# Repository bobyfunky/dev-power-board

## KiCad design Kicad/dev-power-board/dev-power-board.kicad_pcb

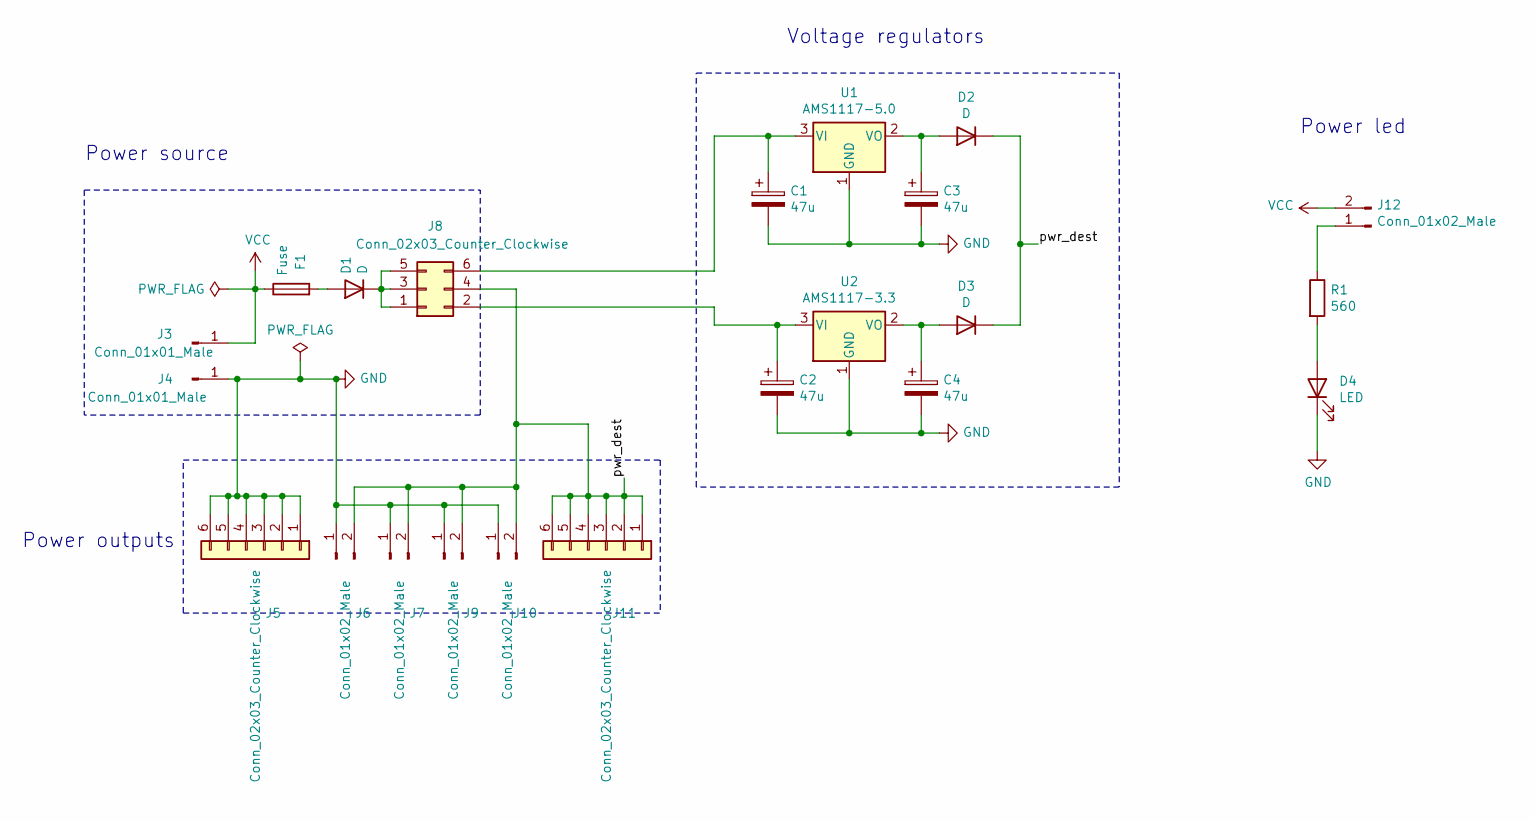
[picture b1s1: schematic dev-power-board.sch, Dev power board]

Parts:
C1, C2, C3, C4: 47u; CP_Elec_6.3x5.4
D1, D2, D3: D; D_0805_2012Metric_Pad1.15x1.40mm_HandSolder
D4: LED; LED_0805_2012Metric
F1: Fuse; Fuse_0805_2012Metric_Pad1.15x1.40mm_HandSolder
J3, J4: Conn_01x01_Male; Banana_Jack_1Pin
J5, J11: Conn_02x03_Counter_Clockwise; PinHeader_1x06_P2.54mm_Vertical
J6, J7, J9, J10, J12: Conn_01x02_Male; PinHeader_1x02_P2.54mm_Vertical
J8: Conn_02x03_Counter_Clockwise; PinHeader_2x03_P2.54mm_Vertical
R1: 560; R_0805_2012Metric_Pad1.15x1.40mm_HandSolder
U1: AMS1117-5.0; SOT-223-3_TabPin2
U2: AMS1117-3.3; SOT-223-3_TabPin2

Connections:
/pwr_dest: D2.1 (K), D3.1 (K), J6.2, J7.2, J8.4, J9.2, J10.2, J11.1, J11.2, J11.3, J11.4, J11.5, J11.6
GND: C1.2, C2.2, C3.2, C4.2, D4.1 (K), J4.1, J5.1, J5.2, J5.3, J5.4, J5.5, J5.6, J6.1, J7.1, J9.1, J10.1, U1.1 (GND), U2.1 (GND)
unnamed: C1.1, J8.6, U1.3 (VI)
unnamed: C2.1, J8.2, U2.3 (VI)
unnamed: C3.1, D2.2 (A), U1.2 (VO)
unnamed: C4.1, D3.2 (A), U2.2 (VO)
unnamed: D1.1 (K), J8.1, J8.3, J8.5
unnamed: D1.2 (A), F1.2
unnamed: D4.2 (A), R1.2
unnamed: J12.1, R1.1
VCC: F1.1, J3.1, J12.2

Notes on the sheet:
Power led
Power source
Power outputs
Voltage regulators

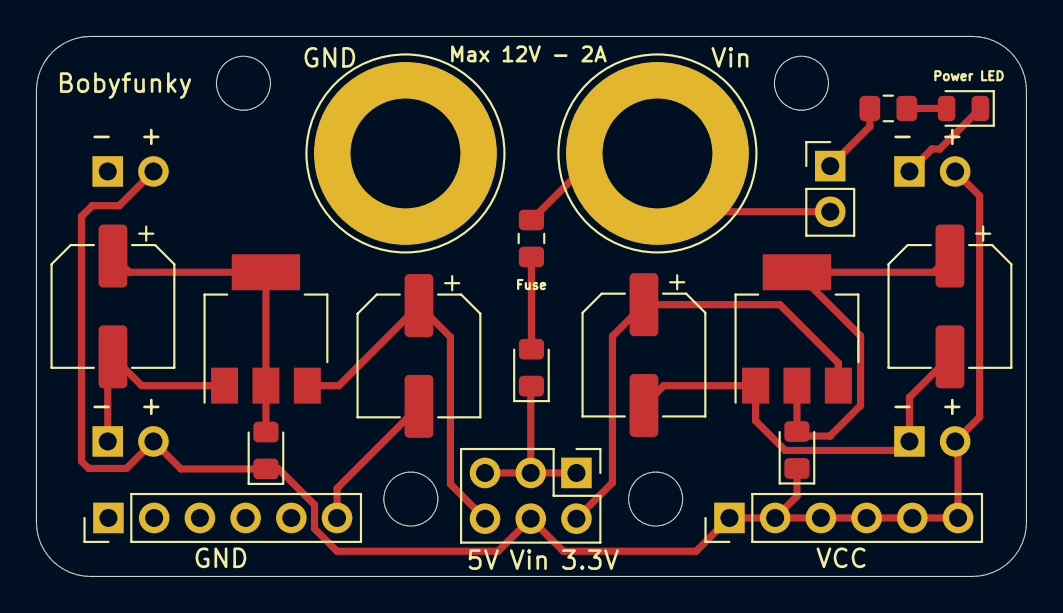
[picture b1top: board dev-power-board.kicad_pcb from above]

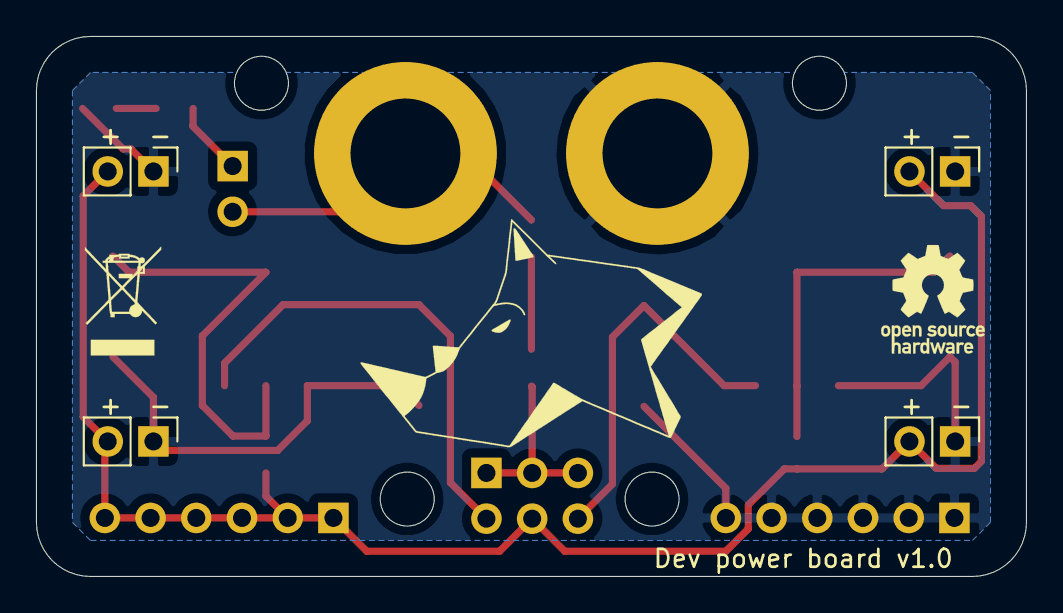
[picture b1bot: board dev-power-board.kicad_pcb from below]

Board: 2 copper layers, 55.0 x 30.0 mm, 22 parts (4 on the bottom side), 11 nets.

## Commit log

2020-09-06 Init repo
2020-09-06 Tracks width + silk
2020-09-21 Drill holes
